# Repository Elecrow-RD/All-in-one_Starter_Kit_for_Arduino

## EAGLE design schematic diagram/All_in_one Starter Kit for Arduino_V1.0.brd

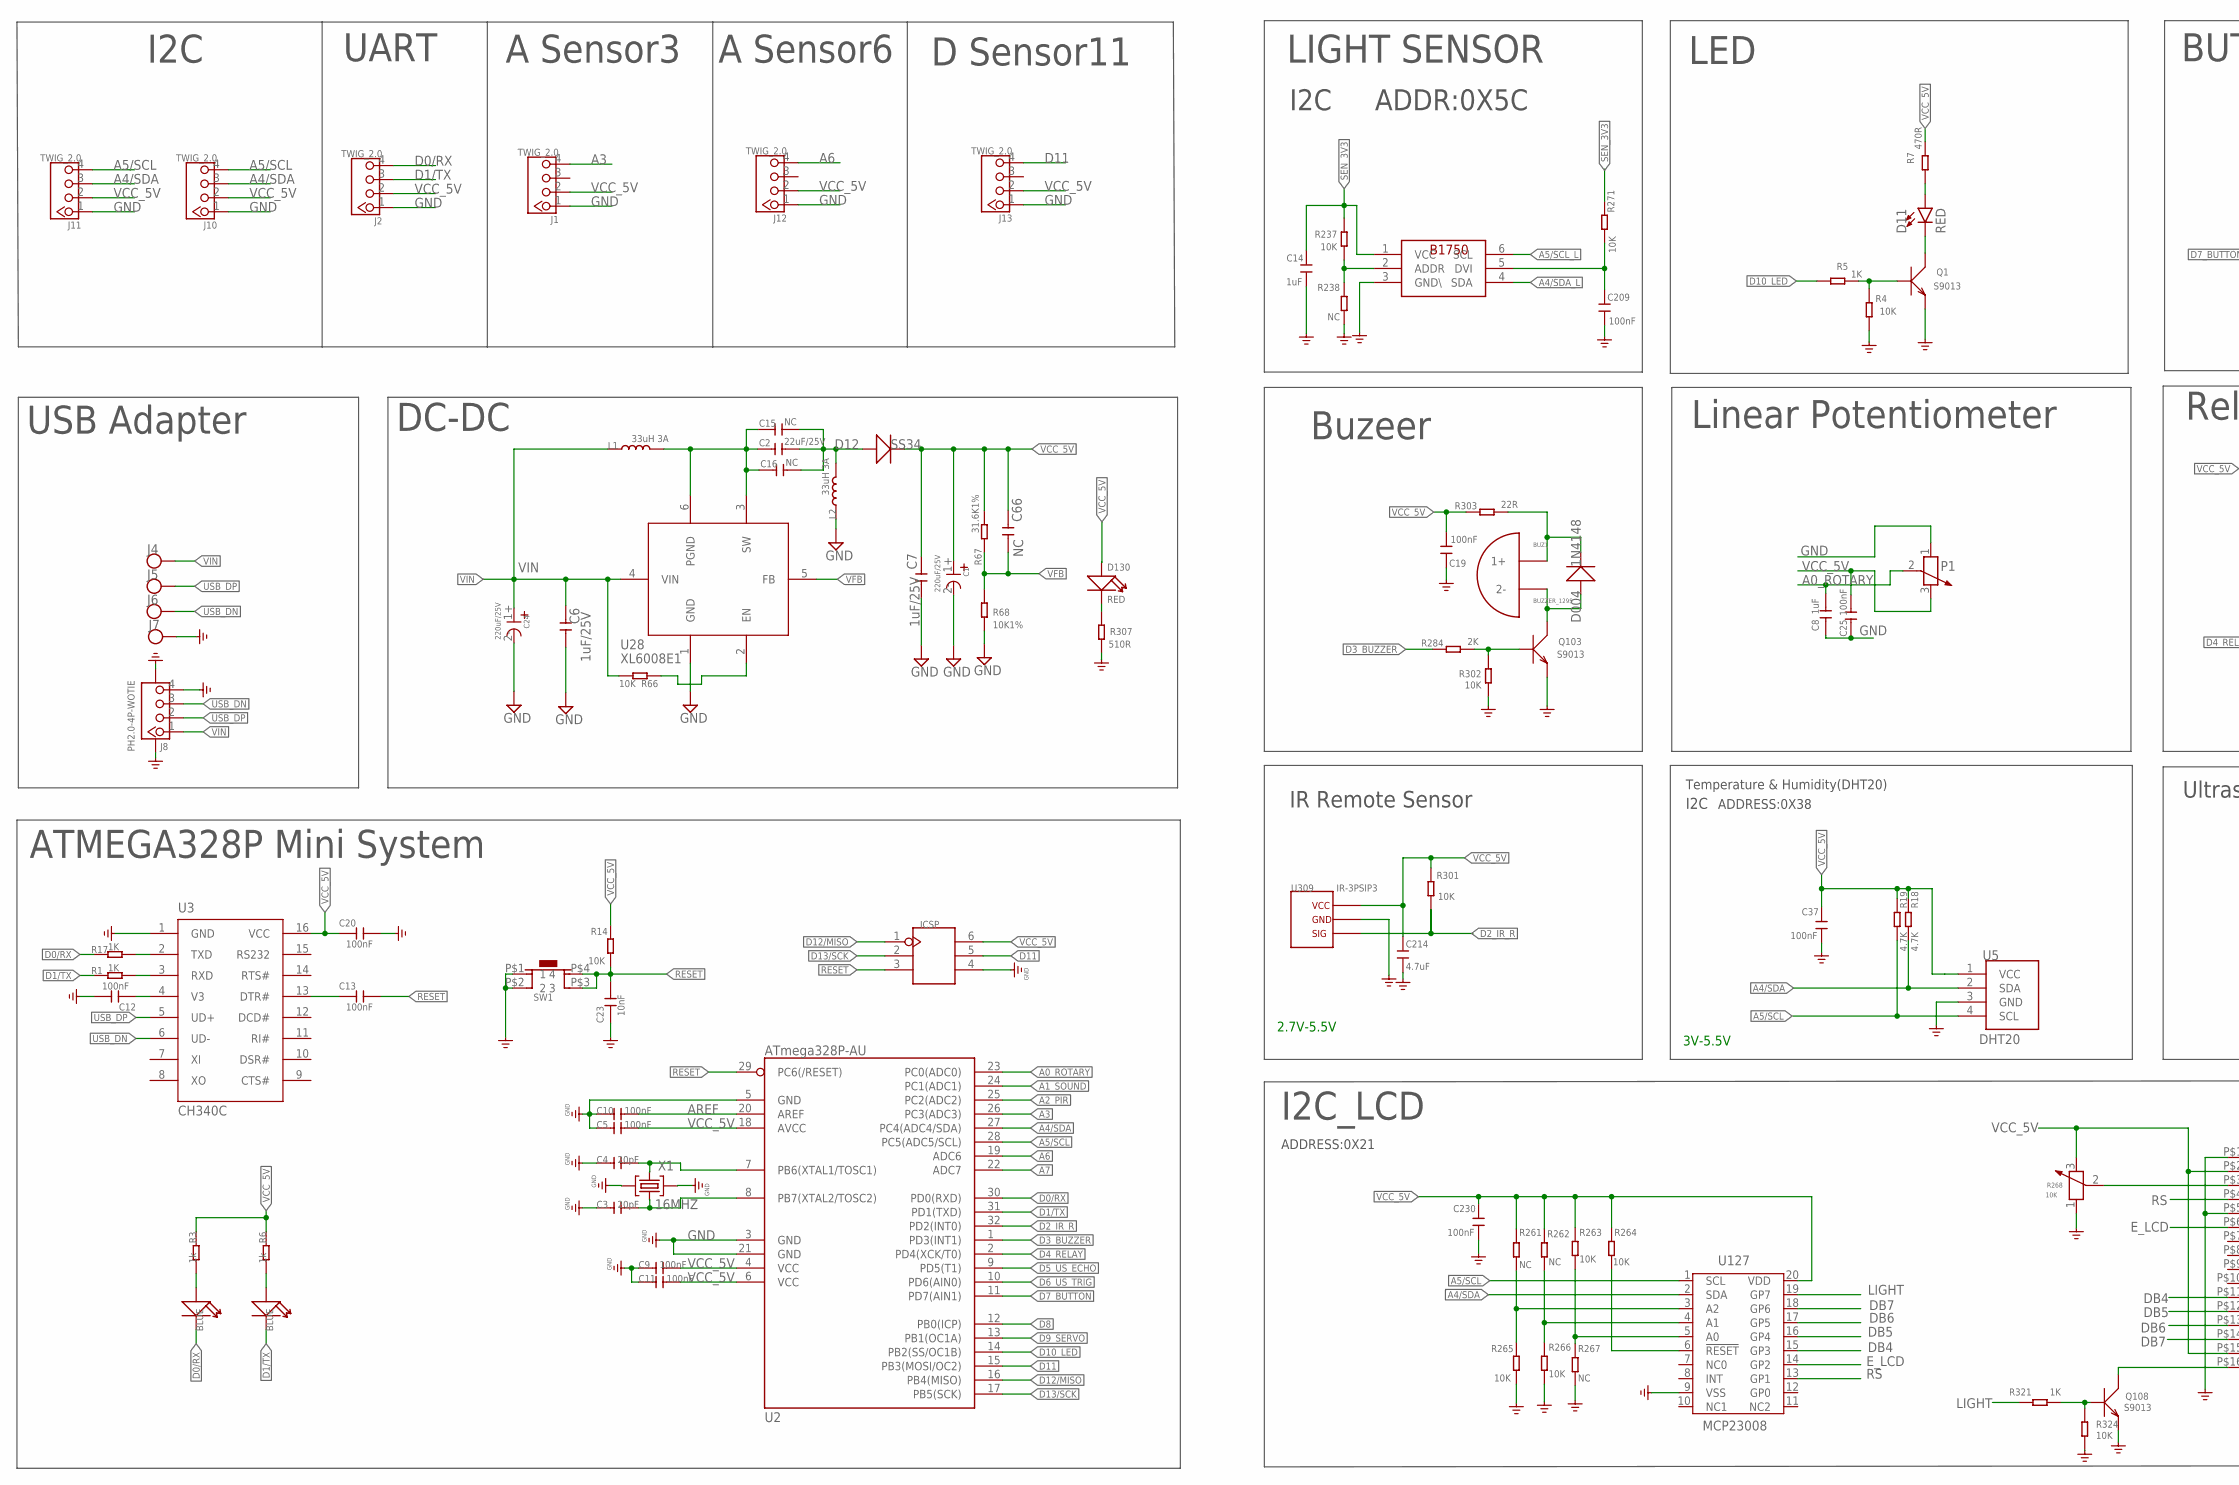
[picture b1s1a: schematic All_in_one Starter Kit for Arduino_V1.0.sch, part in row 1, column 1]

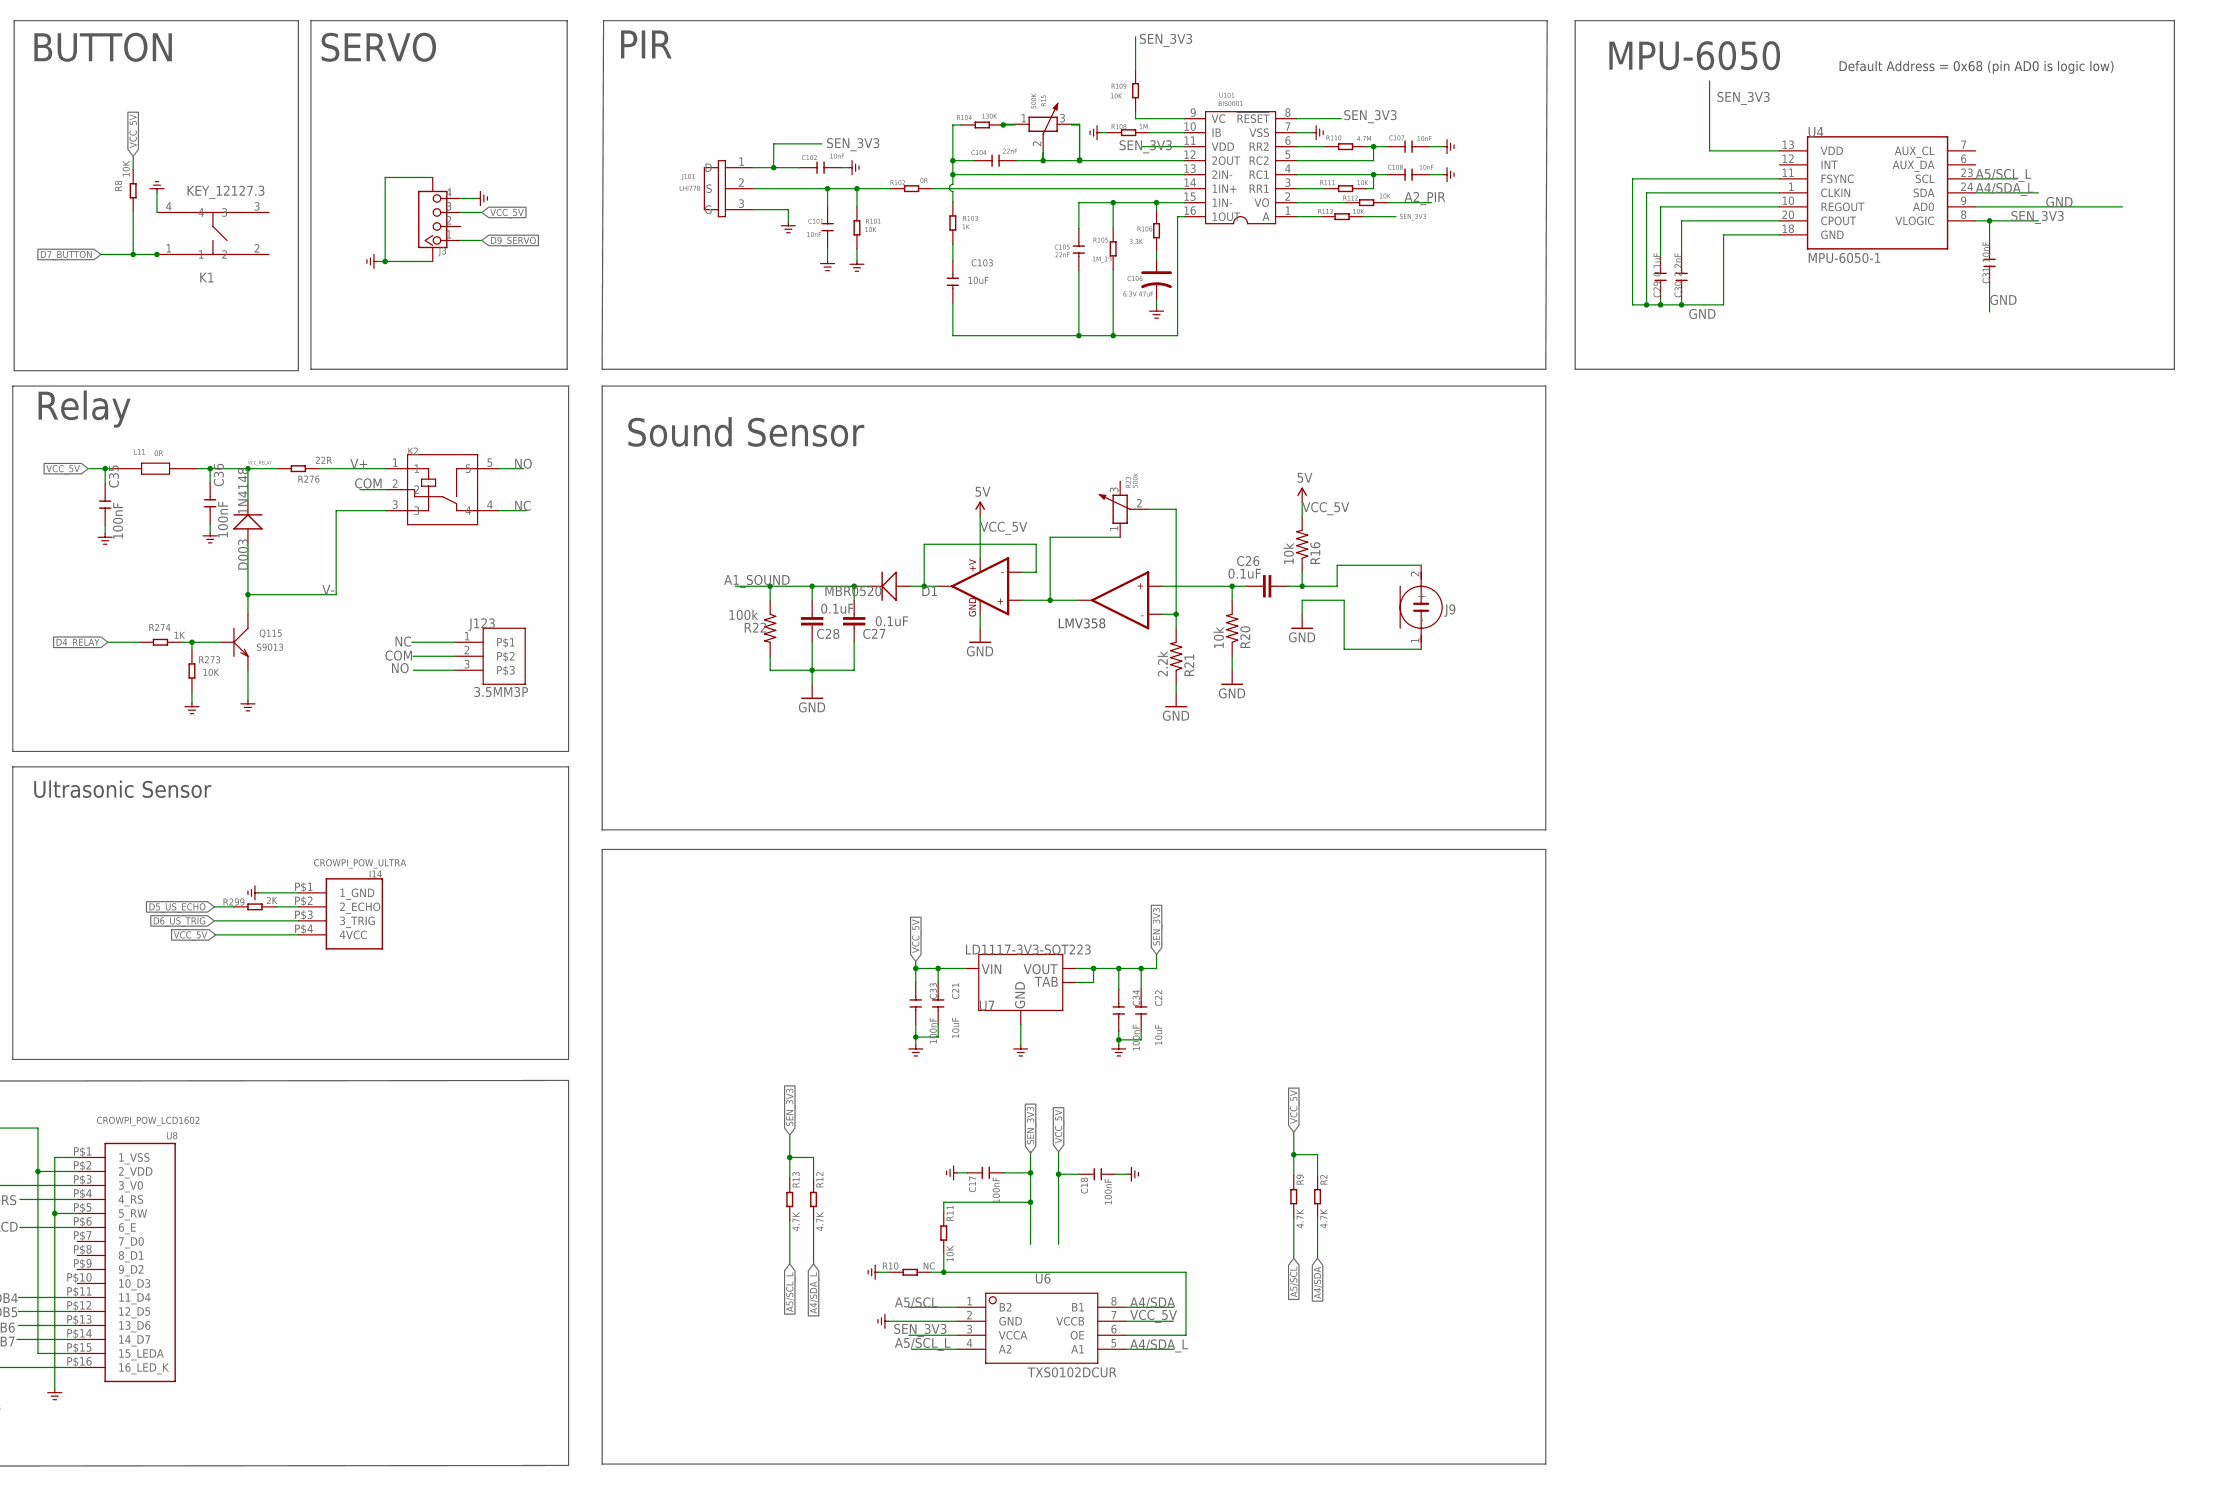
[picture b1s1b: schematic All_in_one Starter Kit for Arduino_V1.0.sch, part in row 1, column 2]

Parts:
BUZ1: BUZZER_1295; BUZZER-D12MM-DIP2
C1, C24: 220uF/25V; CAP_SMD_6.3*5.4MM
C2: 22uF/25V; C0805
C3, C4: 20pF; C0603
C5, C9, C10, C11, C12, C13, C20, C25, C33, C34, C35, C36: 100nF; C0603
C6, C7: 1uF/25V; C0603
C8: 1uF; C0603
C14: 1uF; 0603
C15, C16: NC; C0805
C17, C18, C19, C37, C209, C230: 100nF; 0603
C21, C22: 10uF; C0603
C23, C31, C101, C102, C107, C108: 10nF; C0603
C26, C27, C28: 0.1uF; 0603-CAP
C29: 0.1uF; C0603
C30: 2.2nF; C0603
C66: NC; C0603
C103: 10uF; 0603
C104, C105: 22nF; C0603
C106: 6.3V 47uF; AVX-A
C214: 4.7uF; 0603
D1: MBR0520; SOD123-2.7X1.6
D003, D004: 1N4148; D_SOD123
D11: RED; LED-8MM
D12: SS34; SMA
D13, D14: BLUE; LED-0603
D130: RED; LED_0603_SMT
ICSP: 2.54-2x3p male; 2X3P-2.54
J1, J2, J10, J11, J12, J13: TWIG_2.0; 2.0_1X4
J3: A_XBJ_CONNECTOR_TWIG-4P-2.0-SMD-FEMALE-REINFORCE9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; A_XBJ_CONNECTOR_4P-SMD-2.0-90D
J4, J5, J6, J7: TP-SMDTP-SMD-2X4MM; TP-SMD-2X4MM
J8: PH2.0-4P-WOTIE; PH2.0-4P
J9: TEMPLATE_MIC-6MM; TEMPLATE_2P-D6MM
J14: CROWPI_POW_ULTRA
J101: LHI778; 3P-D8.1MM
J123: 3.5MM3P; 3.5MM*3P
K1: KEY_12127.3; KEY_12*12*7.3
K2: RELAY-SRD; REY5-6-19.1X15.5X15.3MM
L1, L2: 33uH 3A; L1040-SMD
L11: 0R; 201209
P1: R-POTENTIOMETER; 3P-SQUA-45.6X10X5.8H
Q1, Q103, Q108, Q115: S9013; SOT23@1
R1, R5, R17, R103, R274, R321: 1K; R0603
R2, R9, R12, R13, R18, R19: 4.7K; R0603
R3, R6: 1k; R0603
R4, R8, R11, R14, R66, R101, R109, R111, R112, R113, R237, R263, R264, R265, R266, R271, R273, R301, R302, R324: 10K; R0603
R7: 470R; R0603
R10, R238, R261, R262, R267: NC; R0603
R15: 500K; 3P-SMD-SQUA-3.6X3.3
R16, R20: 10k; 0603-RES
R21: 2.2k; 0603-RES
R22: 100k; 0603-RES
R23: 500k; 3P-SMD-SQUA-3.6X3.3
R67: 31.6K1%; R0603
R68: 10K1%; R0603
R102: 0R; R0603
R104: 130K; R0603
R105: 1M_1%; R0603
R106: 3.3K; R0603
R108: 1M; R0603
R110: 4.7M; R0603
R268: 10K; 3P-SMD-SQUA-3.6X3.3
R276, R303: 22R; R0603
R284, R299: 2K; R0603
R307: 510R; R0603
SW1: BUTTON-4P-SMD4.2X3.2; BUTTON-SMD4P-4.2X3.2X2.5
U1: LMV358; SO08
U2: ATmega328P-AU; TQFP32
U3: CH340C; SOP-16
U4: MPU-6050-1; QFN-24-4MM2
U5: DHT20; CROWTAIL-DHT20-V1.0-20211013_DHT20
U6: TXS0102DCUR; VSSOP-8
U7: LD1117-3V3-SOT223; SOT223
U8: CROWPI_POW_LCD1602; CROWPI_POW_LCD1206
U28: XL6008E1; TO252-5
U101: BIS0001; SOP16
U121: BH1750; BH1750-WSOF-6
U127: MCP23008; SSOP20
U309: IR-3PSIP3; VS1838B-SIP3
X1: 16MHZ; CRYSTAL-3.2-2.5

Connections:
A0_ROTARY: C8.2, P1.2 (3), U2.23 (PC0(ADC0))
A1_SOUND: C27.2, C28.2, D1.2 (-), R22.1, U2.24 (PC1(ADC1))
A2_PIR: R112.1, U2.25 (PC2(ADC2))
A3: J1.4, U2.26 (PC3(ADC3))
A4/SDA: J10.3, J11.3, R2.2, R18.2, U2.27 (PC4(ADC4/SDA)), U5.2 (SDA), U6.8 (B1), U127.2 (SDA)
A4/SDA_L: R12.2, U4.24 (SDA), U6.5 (A1), U121.4 (SDA)
A5/SCL: J10.4, J11.4, R9.2, R19.2, U2.28 (PC5(ADC5/SCL)), U5.4 (SCL), U6.1 (B2), U127.1 (SCL)
A5/SCL_L: R13.2, U4.23 (SCL), U6.4 (A2), U121.6 (SCL)
A6: J12.4, U2.19 (ADC6)
A7: U2.22 (ADC7)
AREF: C10.2, U2.20 (AREF)
COM: J123.2, K2.2
D0/RX: D13.-, J2.4, R17.1, U2.30 (PD0(RXD))
D1/TX: D14.-, J2.3, R1.1, U2.31 (PD1(TXD))
D2_IR_R: R301.2, U2.32 (PD2(INT0)), U309.3
D3_BUZZER: R284.1, U2.1 (PD3(INT1))
D4_RELAY: R274.2, U2.2 (PD4(XCK/T0))
D5_US_ECHO: R299.2, U2.9 (PD5(T1))
D6_US_TRIG: J14.P$3 (3_TRIG), U2.10 (PD6(AIN0))
D7_BUTTON: K1.1, R8.2, U2.11 (PD7(AIN1))
D8: U2.12 (PB0(ICP))
D9_SERVO: J3.1, U2.13 (PB1(OC1A))
D10_LED: R5.2, U2.14 (PB2(SS/OC1B))
D11: ICSP.5, J13.4, U2.15 (PB3(MOSI/OC2))
D12/MISO: ICSP.1, U2.16 (PB4(MISO))
D13/SCK: ICSP.2, U2.17 (PB5(SCK))
DB4: U8.P$11 (11_D4), U127.15 (GP3)
DB5: U8.P$12 (12_D5), U127.16 (GP4)
DB6: U8.P$13 (13_D6), U127.17 (GP5)
DB7: U8.P$14 (14_D7), U127.18 (GP6)
E_LCD: U8.P$6 (6_E), U127.14 (GP2)
GND: C1.2-, C3.1, C4.1, C5.1, C6.1, C7.1, C8.1, C9.1, C10.1, C11.1, C12.2, C14.1, C17.2, C18.1, C19.2, C20.2, C21.2, C22.2, C23.1, C24.2-, C25.1, C27.1, C28.1, C29.1, C30.1, C31.1, C33.2, C34.2, C35.1, C36.1, C37.1, C101.1, C102.1, C106.-, C107.2, C108.2, C209.1, C214.1, C230.1, ICSP.4, J1.1, J2.1, J3.4, J3.SS1, J3.SS2, J7.1, J8.4, J8.5 (SS1), J8.6 (SS2), J9.1 (-), J10.1, J11.1, J12.1, J13.1, J14.P$1 (1_GND), J101.3 (G), K1.4, L2.1, P1.1, Q1.2 (E), Q103.2 (E), Q108.2 (E), Q115.2 (E), R4.1, R10.1, R20.1, R21.1, R22.2, R68.2, R101.1, R108.1, R238.1, R265.2, R266.2, R267.1, R268.1, R273.1, R302.1, R307.2, R324.2, SW1.P$1 (1), SW1.P$2 (2), U1.4 (GND), U2.3 (GND), U2.5 (GND), U2.21 (GND), U3.1 (GND), U4.1 (CLKIN), U4.9 (AD0), U4.11 (FSYNC), U4.18 (GND), U5.3 (GND), U6.2 (GND), U7.1 (GND), U8.P$1 (1_VSS), U8.P$5 (5_RW), U28.1 (GND), U101.7 (VSS), U121.3 (GND\), U127.9 (VSS), U309.2, X1.2 (GND), X1.4 (GND)
LIGHT: R321.2, U127.19 (GP7)
unnamed: R111.1, U101.3 (RR1)
unnamed: Q108.1 (B), R321.1, R324.1
unnamed: R261.1, R265.1, U127.3 (A2)
unnamed: R262.1, R266.1, U127.4 (A1)
unnamed: R263.2, R267.2, U127.5 (A0)
unnamed: R264.2, U127.6 (!RESET)
unnamed: R268.2 (3), U8.P$3 (3_V0)
unnamed: D13.+, R3.2
unnamed: C12.1, U3.4 (V3)
unnamed: C13.1, U3.13 (DTR#)
unnamed: C4.2, U2.7 (PB6(XTAL1/TOSC1)), X1.3 (C2)
unnamed: C3.2, U2.8 (PB7(XTAL2/TOSC2)), X1.1 (C1)
unnamed: C108.1, R111.2, U101.4 (RC1)
unnamed: Q1.1 (B), R4.2, R5.1
unnamed: D11.2 (C), Q1.3 (C)
unnamed: D11.1 (A), R7.2
unnamed: D14.+, R6.2
unnamed: R66.1, U28.2 (EN)
unnamed: C2.2, C15.2, C16.2, D12.2 (+), L2.2
unnamed: Q108.3 (C), U8.P$16 (16_LED_K)
unnamed: R112.2, U101.2 (VO)
unnamed: R17.2, U3.2 (TXD)
unnamed: R1.2, U3.3 (RXD)
unnamed: R10.2, R11.2, U6.6 (OE)
unnamed: R110.2, U101.6 (RR2)
unnamed: C107.1, R110.1, U101.5 (RC2)
unnamed: C104.2, R15.2 (3), R15.3 (2), U101.12 (2OUT)
unnamed: C104.1, R103.2, R104.2, U101.13 (2IN-)
unnamed: R109.2, U101.9 (VC)
unnamed: R108.2, U101.10 (IB)
unnamed: C101.2, J101.2 (S), R101.2, R102.2
unnamed: C103.2, C105.1, R105.1, U101.16 (1OUT)
unnamed: C105.2, R105.2, R106.2, U101.15 (1IN-)
unnamed: C209.2, R271.2, U121.5 (DVI)
unnamed: C103.1, R103.1
unnamed: C106.+, R106.1
unnamed: R113.2, U101.1 (A)
unnamed: R102.1, U101.14 (1IN+)
unnamed: R15.1, R104.1
unnamed: C26.1, J9.2 (+), R16.1
unnamed: C26.2, R20.2, U1.5 (+IN2)
unnamed: R21.2, R23.2 (3), U1.6 (-IN2)
unnamed: D1.1 (+), U1.1 (OUT1), U1.2 (-IN1)
unnamed: R23.1, U1.3 (+IN1), U1.7 (OUT2)
unnamed: C29.2, U4.10 (REGOUT)
unnamed: C30.2, U4.20 (CPOUT)
unnamed: D130.2 (2_K), R307.1
unnamed: C2.1, C15.1, C16.1, L1.2, U28.3 (SW), U28.6 (PGND)
unnamed: R237.1, R238.2, U121.2 (ADDR)
unnamed: Q115.1 (B), R273.2, R274.1
unnamed: J14.P$2 (2_ECHO), R299.1
unnamed: Q103.1 (B), R284.2, R302.2
unnamed: BUZ1.2 (2-), D004.+, Q103.3 (C)
unnamed: BUZ1.1 (1+), D004.-, R303.2
NC: J123.1, K2.4
NO: J123.3, K2.5
RESET: C13.2, C23.2, ICSP.3, R14.2, SW1.P$3 (3), SW1.P$4 (4), U2.29 (PC6(/RESET))
RS: U8.P$4 (4_RS), U127.13 (GP1)
SEN_3V3: C14.2, C17.1, C22.1, C31.2, C34.1, C102.2, J101.1 (D), R11.1, R12.1, R13.1, R109.1, R113.1, R237.2, R271.1, U4.8 (VLOGIC), U4.13 (VDD), U6.3 (VCCA), U7.2 (VOUT), U7.4 (TAB), U101.8 (!RESET), U101.11 (VDD), U121.1 (VCC)
USB_DN: J6.1, J8.3, U3.6 (UD-)
USB_DP: J5.1, J8.2, U3.5 (UD+)
V+: K2.1, R276.2
V-: D003.+, K2.3, Q115.3 (C)
VCC_5V: C1.1+, C5.2, C7.2, C9.2, C11.2, C18.2, C19.1, C20.1, C21.1, C25.2, C33.1, C35.2, C37.2, C66.2, C214.2, C230.2, D12.1 (-), D130.1 (1_A), ICSP.6, J1.2, J2.2, J3.3, J10.2, J11.2, J12.2, J13.2, J14.P$4 (4VCC), L11.1, P1.3 (2), R2.1, R3.1, R6.1, R7.1, R8.1, R9.1, R14.1, R16.2, R18.1, R19.1, R67.1, R261.2, R262.2, R263.1, R264.1, R268.3 (2), R301.1, R303.1, U1.8 (+V), U2.4 (VCC), U2.6 (VCC), U2.18 (AVCC), U3.16 (VCC), U5.1 (VCC), U6.7 (VCCB), U7.3 (VIN), U8.P$2 (2_VDD), U8.P$15 (15_LEDA), U127.20 (VDD), U309.1
VCC_RELAY: C36.2, D003.-, L11.2, R276.1
VFB: C66.1, R67.2, R68.1, U28.5 (FB)
VIN: C6.2, C24.1+, J4.1, J8.1, L1.1, R66.2, U28.4 (VIN)

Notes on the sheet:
I2C_LCD
LIGHT SENSOR
SERVO
Ultrasonic Sensor
IR Remote Sensor
I2C
Temperature & Humidity(DHT20)
Buzeer
PIR
Relay
2.7V-5.5V
3V-5.5V
ADDRESS:0X38
UART
ADDRESS:0X21
A Sensor3
A Sensor6
LED
BUTTON
Linear Potentiometer
DC-DC
ATMEGA328P Mini System
USB Adapter
ADDR:0X5C
Sound Sensor
LMV358
Default Address = 0x68 (pin AD0 is logic low)
MPU-6050
D Sensor11

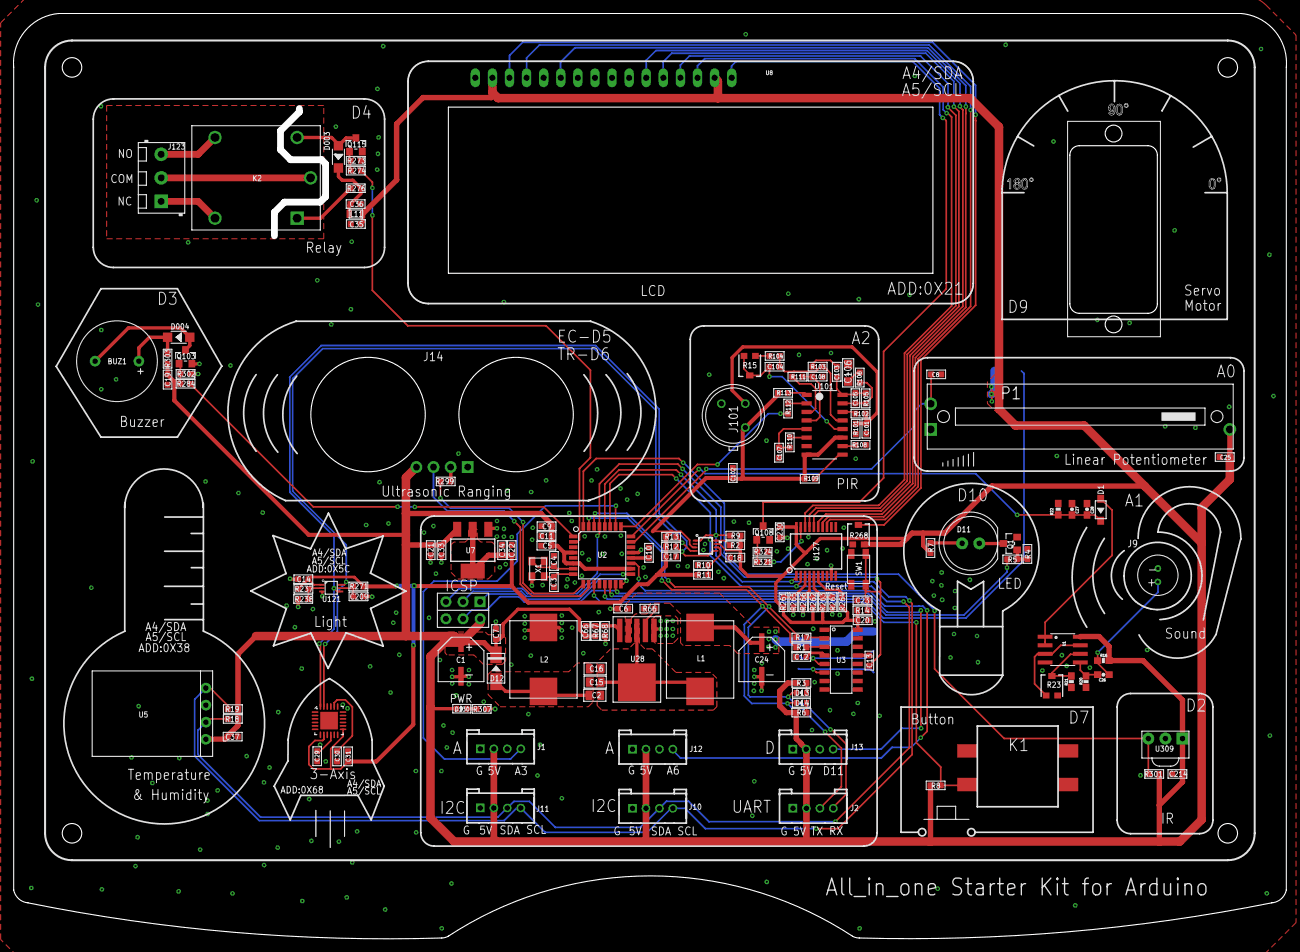
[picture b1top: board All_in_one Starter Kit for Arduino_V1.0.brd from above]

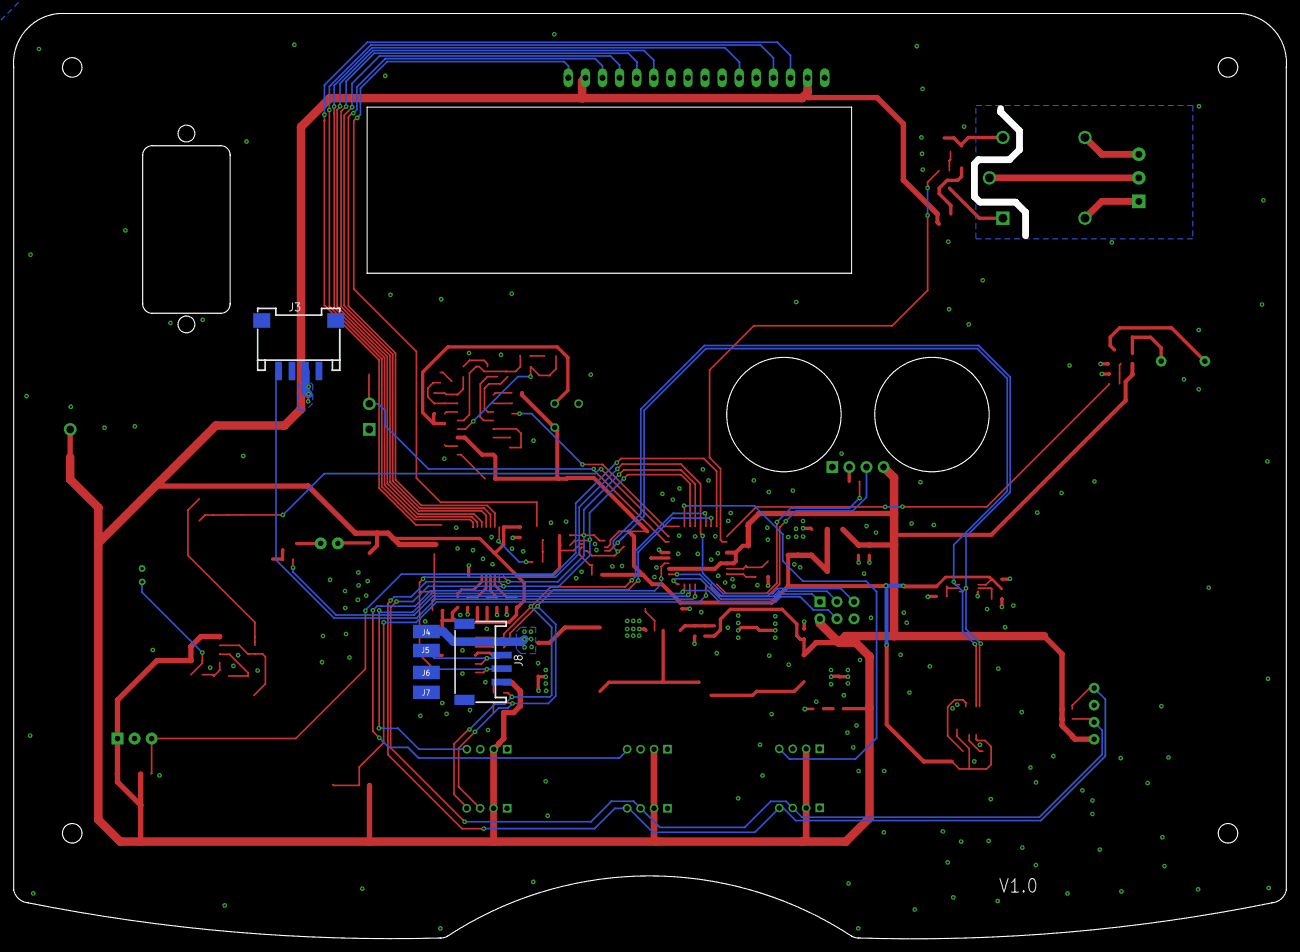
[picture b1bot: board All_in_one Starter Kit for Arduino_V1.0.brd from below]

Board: 2 copper layers, 189.2 x 137.5 mm, 159 parts (6 on the bottom side), 98 nets.
